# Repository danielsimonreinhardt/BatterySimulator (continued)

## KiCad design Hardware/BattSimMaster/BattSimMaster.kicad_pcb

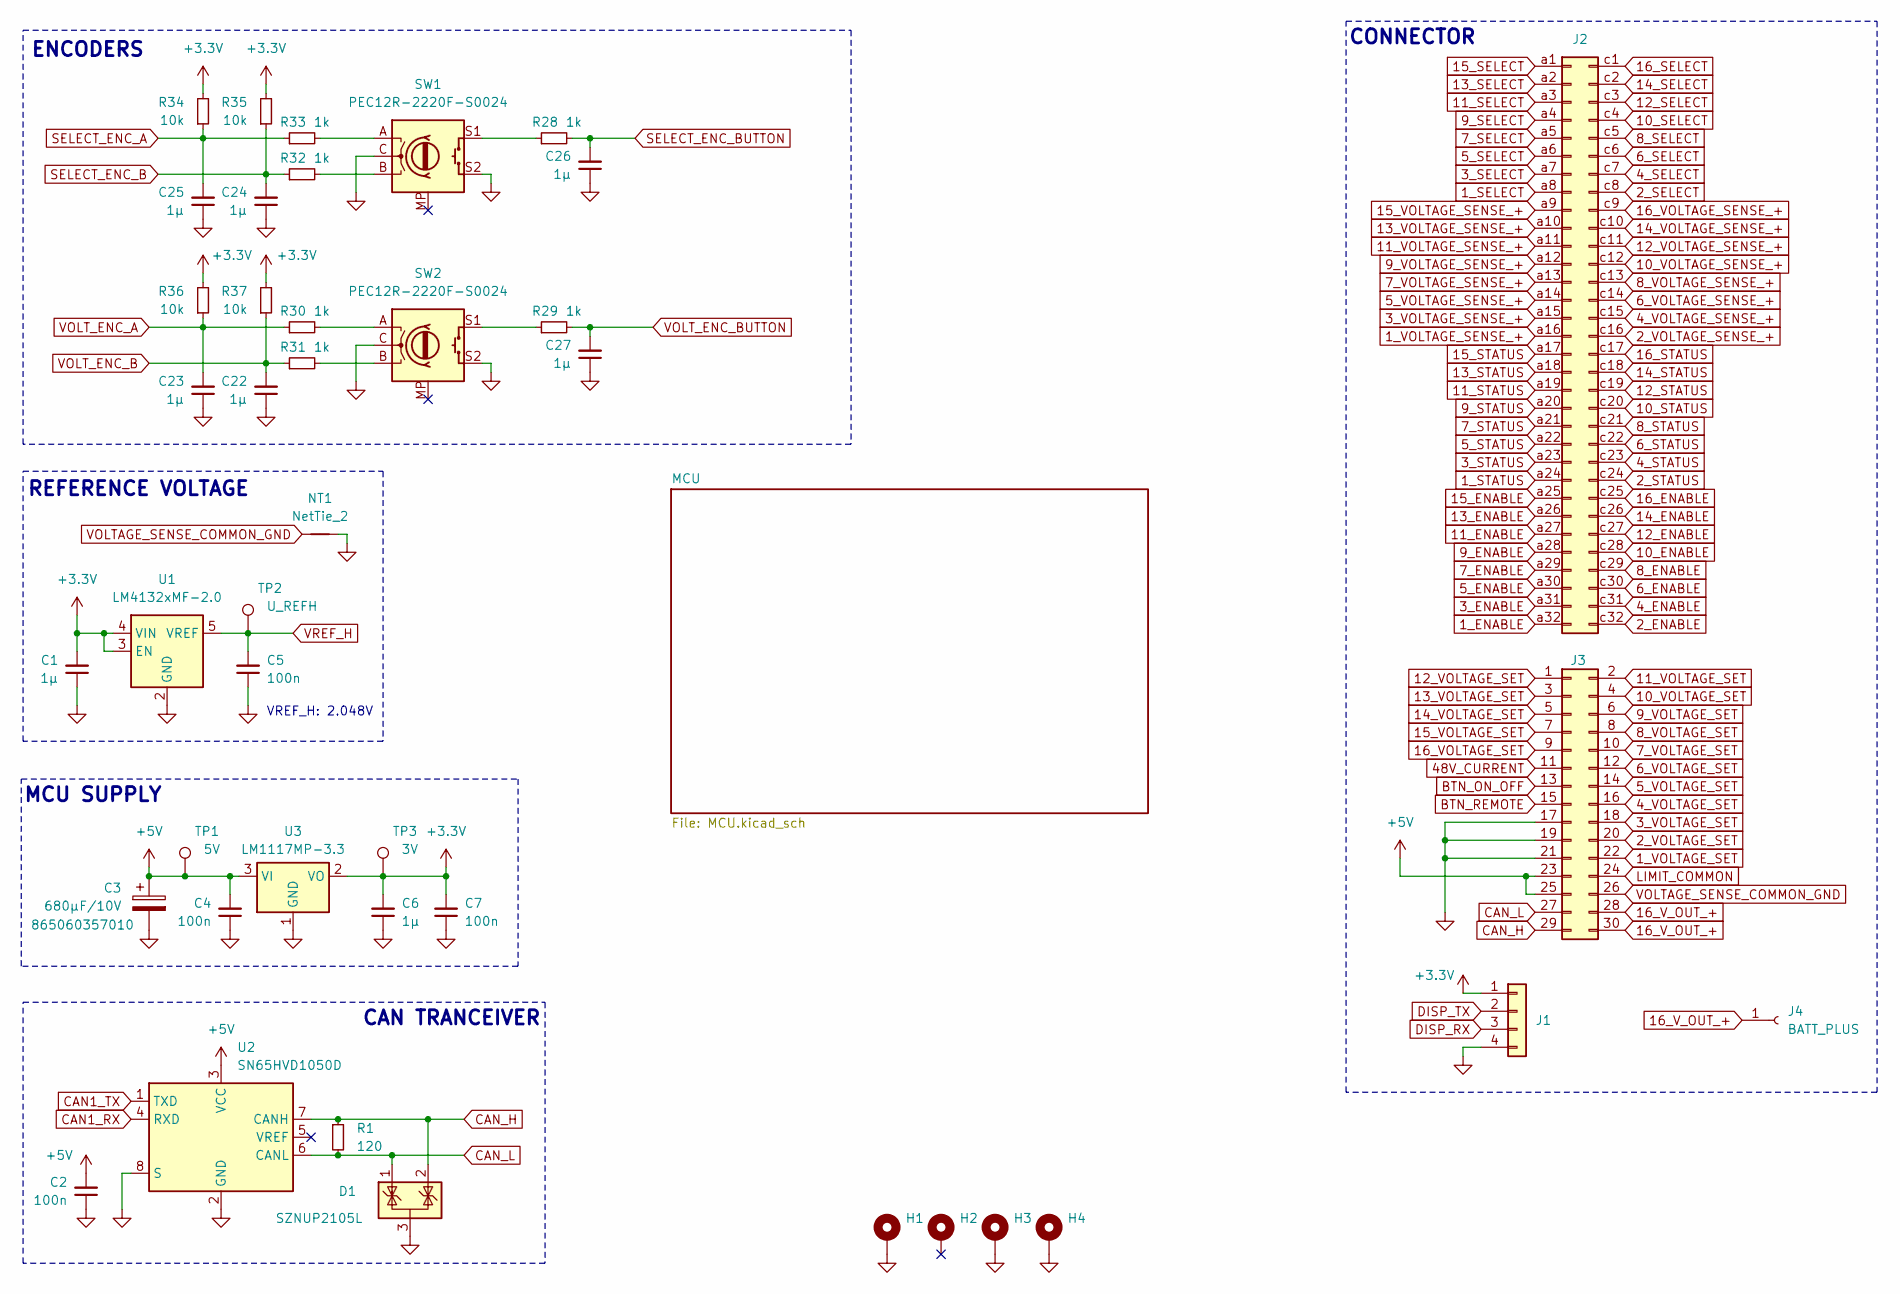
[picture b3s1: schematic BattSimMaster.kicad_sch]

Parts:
C1, C6, C22, C23, C24, C25, C26, C27: 1µ; C_0603_1608Metric_Pad1.08x0.95mm_HandSolder; LCSC Part # C15849
C2, C4, C5, C7: 100n; C_0603_1608Metric_Pad1.08x0.95mm_HandSolder; LCSC Part # C14663
C3: 680µF/10V; CP_Elec_10x10.5
D1: SZNUP2105L; SOT-23
H1, H2, H3, H4: MountingHole_Pad; MountingHole_3.2mm_M3_Pad_Via
J1: Conn_01x04; JST_PH_B4B-PH-K_1x04_P2.00mm_Vertical
J2: DIN41612_02x32_AC; DIN41612_C_2x32_Male_Horizontal_THT
J3: Conn_02x15_Odd_Even; PinSocket_2x15_P2.54mm_Vertical
J4: BATT_PLUS; Banana_Cliff_FCR7350R_S16N-PC_Horizontal
NT1: NetTie_2; NetTie-2_SMD_Pad0.5mm
R1: 120; R_0603_1608Metric_Pad0.98x0.95mm_HandSolder; LCSC C22787
R28, R29, R30, R31, R32, R33: 1k; R_0603_1608Metric; LCSC Part # C21190
R34, R35, R36, R37: 10k; R_0603_1608Metric_Pad0.98x0.95mm_HandSolder; LCSC C25804
SW1, SW2: PEC12R-2220F-S0024; RotaryEncoder_Bourns_Horizontal_PEC12R-2x17F-Sxxxx
TP1: 5V; TestPoint_Pad_D1.0mm
TP2: U_REFH; TestPoint_Pad_D1.0mm
TP3: 3V; TestPoint_Pad_D1.0mm
U1: LM4132xMF-2.0; SOT-23-5; LCSC C2157325
U2: SN65HVD1050D; SOIC-8_3.9x4.9mm_P1.27mm
U3: LM1117MP-3.3; SOT-223-3_TabPin2; LCSC Part # C126027

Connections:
1_ENABLE: J2.a32; also elsewhere on the board
1_SELECT: J2.a8; also elsewhere on the board
1_STATUS: J2.a24; also elsewhere on the board
1_VOLTAGE_SENSE_+: J2.a16; also elsewhere on the board
1_VOLTAGE_SET: J3.22; also elsewhere on the board
2_ENABLE: J2.c32; also elsewhere on the board
2_SELECT: J2.c8; also elsewhere on the board
2_STATUS: J2.c24; also elsewhere on the board
2_VOLTAGE_SENSE_+: J2.c16; also elsewhere on the board
2_VOLTAGE_SET: J3.20; also elsewhere on the board
3_ENABLE: J2.a31; also elsewhere on the board
3_SELECT: J2.a7; also elsewhere on the board
3_STATUS: J2.a23; also elsewhere on the board
3_VOLTAGE_SENSE_+: J2.a15; also elsewhere on the board
3_VOLTAGE_SET: J3.18; also elsewhere on the board
4_ENABLE: J2.c31; also elsewhere on the board
4_SELECT: J2.c7; also elsewhere on the board
4_STATUS: J2.c23; also elsewhere on the board
4_VOLTAGE_SENSE_+: J2.c15; also elsewhere on the board
4_VOLTAGE_SET: J3.16; also elsewhere on the board
5_ENABLE: J2.a30; also elsewhere on the board
5_SELECT: J2.a6; also elsewhere on the board
5_STATUS: J2.a22; also elsewhere on the board
5_VOLTAGE_SENSE_+: J2.a14; also elsewhere on the board
5_VOLTAGE_SET: J3.14; also elsewhere on the board
6_ENABLE: J2.c30; also elsewhere on the board
6_SELECT: J2.c6; also elsewhere on the board
6_STATUS: J2.c22; also elsewhere on the board
6_VOLTAGE_SENSE_+: J2.c14; also elsewhere on the board
6_VOLTAGE_SET: J3.12; also elsewhere on the board
7_ENABLE: J2.a29; also elsewhere on the board
7_SELECT: J2.a5; also elsewhere on the board
7_STATUS: J2.a21; also elsewhere on the board
7_VOLTAGE_SENSE_+: J2.a13; also elsewhere on the board
7_VOLTAGE_SET: J3.10; also elsewhere on the board
8_ENABLE: J2.c29; also elsewhere on the board
8_SELECT: J2.c5; also elsewhere on the board
8_STATUS: J2.c21; also elsewhere on the board
8_VOLTAGE_SENSE_+: J2.c13; also elsewhere on the board
8_VOLTAGE_SET: J3.8; also elsewhere on the board
9_ENABLE: J2.a28; also elsewhere on the board
9_SELECT: J2.a4; also elsewhere on the board
9_STATUS: J2.a20; also elsewhere on the board
9_VOLTAGE_SENSE_+: J2.a12; also elsewhere on the board
9_VOLTAGE_SET: J3.6; also elsewhere on the board
10_ENABLE: J2.c28; also elsewhere on the board
10_SELECT: J2.c4; also elsewhere on the board
10_STATUS: J2.c20; also elsewhere on the board
10_VOLTAGE_SENSE_+: J2.c12; also elsewhere on the board
10_VOLTAGE_SET: J3.4; also elsewhere on the board
11_ENABLE: J2.a27; also elsewhere on the board
11_SELECT: J2.a3; also elsewhere on the board
11_STATUS: J2.a19; also elsewhere on the board
11_VOLTAGE_SENSE_+: J2.a11; also elsewhere on the board
11_VOLTAGE_SET: J3.2; also elsewhere on the board
12_ENABLE: J2.c27; also elsewhere on the board
12_SELECT: J2.c3; also elsewhere on the board
12_STATUS: J2.c19; also elsewhere on the board
12_VOLTAGE_SENSE_+: J2.c11; also elsewhere on the board
12_VOLTAGE_SET: J3.1; also elsewhere on the board
13_ENABLE: J2.a26; also elsewhere on the board
13_SELECT: J2.a2; also elsewhere on the board
13_STATUS: J2.a18; also elsewhere on the board
13_VOLTAGE_SENSE_+: J2.a10; also elsewhere on the board
13_VOLTAGE_SET: J3.3; also elsewhere on the board
14_ENABLE: J2.c26; also elsewhere on the board
14_SELECT: J2.c2; also elsewhere on the board
14_STATUS: J2.c18; also elsewhere on the board
14_VOLTAGE_SENSE_+: J2.c10; also elsewhere on the board
14_VOLTAGE_SET: J3.5; also elsewhere on the board
15_ENABLE: J2.a25; also elsewhere on the board
15_SELECT: J2.a1; also elsewhere on the board
15_STATUS: J2.a17; also elsewhere on the board
15_VOLTAGE_SENSE_+: J2.a9; also elsewhere on the board
15_VOLTAGE_SET: J3.7; also elsewhere on the board
16_ENABLE: J2.c25; also elsewhere on the board
16_SELECT: J2.c1; also elsewhere on the board
16_STATUS: J2.c17; also elsewhere on the board
16_VOLTAGE_SENSE_+: J2.c9; also elsewhere on the board
16_VOLTAGE_SET: J3.9; also elsewhere on the board
16_V_OUT_+: J3.28, J3.30, J4.1
48V_CURRENT: J3.11; also elsewhere on the board
+3.3V: C1.2, C6.2, C7.2, J1.1, R34.2, R35.2, R36.2, R37.2, TP3.1, U1.3 (EN), U1.4 (VIN), U3.2 (VO); also elsewhere on the board
+5V: C2.2, C3.1, C4.2, J3.23, J3.25, TP1.1, U2.3 (VCC), U3.3 (VI)
BTN_ON_OFF: J3.13; also elsewhere on the board
BTN_REMOTE: J3.15; also elsewhere on the board
CAN1_RX: U2.4 (RXD); also elsewhere on the board
CAN1_TX: U2.1 (TXD); also elsewhere on the board
CAN_H: D1.2 (K), J3.29, R1.1, U2.7 (CANH)
CAN_L: D1.1 (K), J3.27, R1.2, U2.6 (CANL)
DISP_RX: J1.3; also elsewhere on the board
DISP_TX: J1.2; also elsewhere on the board
GND: C1.1, C2.1, C3.2, C4.1, C5.1, C6.1, C7.1, C22.1, C23.1, C24.1, C25.1, C26.1, C27.1, D1.3 (A), H1.1, H3.1, H4.1, J1.4, J3.17, J3.19, J3.21, NT1.2, SW1.C, SW1.S2, SW2.C, SW2.S2, U1.2 (GND), U2.2 (GND), U2.8 (S), U3.1 (GND); also elsewhere on the board
LIMIT_COMMON: J3.24; also elsewhere on the board
unnamed: R28.1, SW1.S1
unnamed: R29.1, SW2.S1
unnamed: R30.2, SW2.A
unnamed: R31.2, SW2.B
unnamed: R32.2, SW1.B
unnamed: R33.2, SW1.A
SELECT_ENC_A: C25.2, R33.1, R34.1; also elsewhere on the board
SELECT_ENC_B: C24.2, R32.1, R35.1; also elsewhere on the board
SELECT_ENC_BUTTON: C26.2, R28.2; also elsewhere on the board
VOLTAGE_SENSE_COMMON_GND: J3.26, NT1.1
VOLT_ENC_A: C23.2, R30.1, R36.1; also elsewhere on the board
VOLT_ENC_B: C22.2, R31.1, R37.1; also elsewhere on the board
VOLT_ENC_BUTTON: C27.2, R29.2; also elsewhere on the board
VREF_H: C5.2, TP2.1, U1.5 (VREF); also elsewhere on the board

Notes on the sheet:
MCU SUPPLY
CONNECTOR
CAN TRANCEIVER
VREF_H: 2.048V
REFERENCE VOLTAGE
ENCODERS

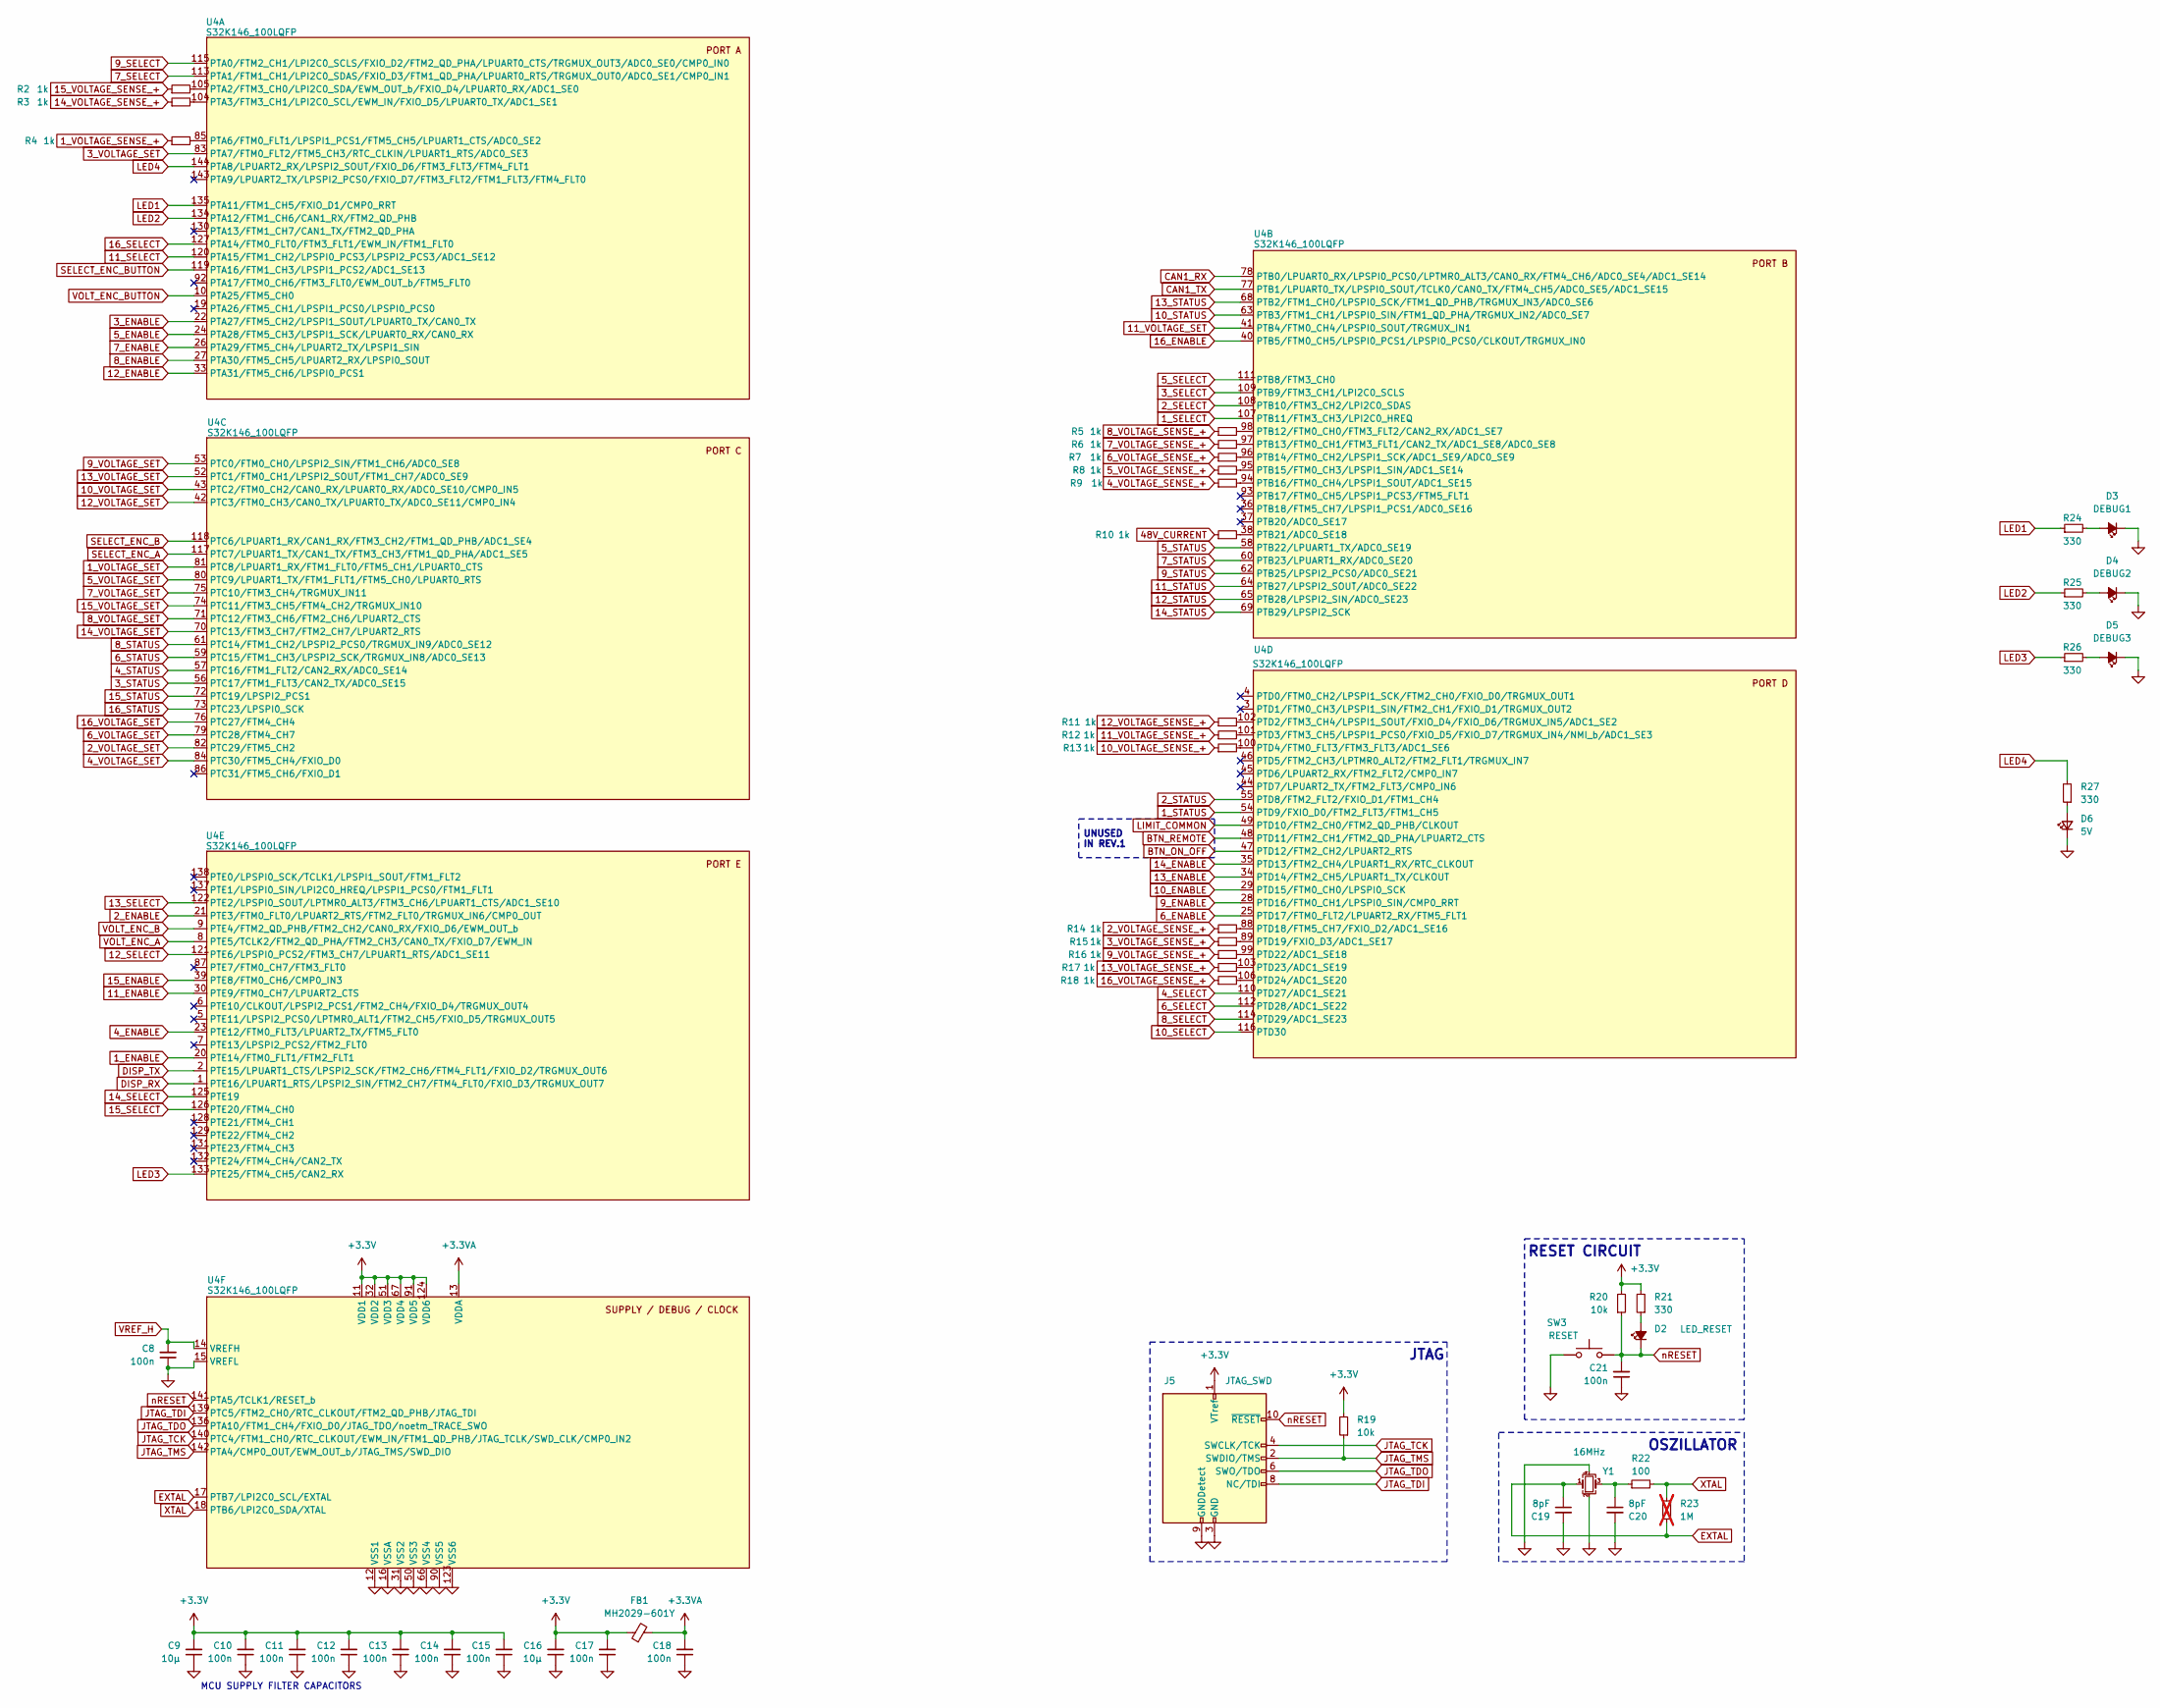
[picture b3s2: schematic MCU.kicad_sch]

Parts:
C8, C10, C11, C12, C13, C14, C15, C17, C18: 100n; C_0603_1608Metric_Pad1.08x0.95mm_HandSolder; LCSC Part # C14663
C9, C16: 10µ; C_0805_2012Metric_Pad1.18x1.45mm_HandSolder; LCSC Part # C15850
C19, C20: 8pF; C_0603_1608Metric_Pad1.08x0.95mm_HandSolder
C21: 100n; C_0603_1608Metric_Pad1.08x0.95mm_HandSolder; LCSC C14663
D2: LED_RESET; LED_0805_2012Metric_Pad1.15x1.40mm_HandSolder; LCSC C2296
D3: DEBUG1; LED_0805_2012Metric; LCSC C2296
D4: DEBUG2; LED_0805_2012Metric
D5: DEBUG3; LED_0805_2012Metric
D6: 5V; LED_D3.0mm_Horizontal_O1.27mm_Z6.0mm
FB1: MH2029-601Y; L_0805_2012Metric_Pad1.05x1.20mm_HandSolder; LCSC Part # C840592
J5: JTAG_SWD; SAMTEC_FTSH-105-01-F-DV-P-TR; LCSC Part # C5136979
R2, R3, R4, R5, R6, R7, R8, R9, R10, R11, R12, R13, R14, R15, R16, R17, R18: 1k; R_0603_1608Metric; LCSC Part # C21190
R19, R20: 10k; R_0603_1608Metric_Pad0.98x0.95mm_HandSolder; LCSC C25804
R21: 330; R_0603_1608Metric_Pad0.98x0.95mm_HandSolder; LCSC C23138
R22: 100; R_0603_1608Metric_Pad0.98x0.95mm_HandSolder
R23: 1M; R_0402_1005Metric_Pad0.72x0.64mm_HandSolder; not fitted
R24, R25, R26: 330; R_0603_1608Metric; LCSC C23138
R27: 330; R_0603_1608Metric
SW3: RESET; SW_PUSH_6mm
U4: S32K146_100LQFP; LQFP-144_20x20mm_P0.5mm; LCSC Part # C427701
Y1: 16MHz; Crystal_SMD_3225-4Pin_3.2x2.5mm; LCSC C13738

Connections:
1_ENABLE: U4.20 (PTE14/FTM0_FLT1/FTM2_FLT1); also elsewhere on the board
1_SELECT: U4.107 (PTB11/FTM3_CH3/LPI2C0_HREQ); also elsewhere on the board
1_STATUS: U4.54 (PTD9/FXIO_D0/FTM2_FLT3/FTM1_CH5); also elsewhere on the board
1_VOLTAGE_SENSE_+: R4.1; also elsewhere on the board
1_VOLTAGE_SET: U4.81 (PTC8/LPUART1_RX/FTM1_FLT0/FTM5_CH1/LPUA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); also elsewhere on the board
2_ENABLE: U4.21 (PTE3/FTM0_FLT0/LPUART2_RTS/FTM2_FLT0/TR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); also elsewhere on the board
2_SELECT: U4.108 (PTB10/FTM3_CH2/LPI2C0_SDAS); also elsewhere on the board
2_STATUS: U4.55 (PTD8/FTM2_FLT2/FXIO_D1/FTM1_CH4); also elsewhere on the board
2_VOLTAGE_SENSE_+: R14.1; also elsewhere on the board
2_VOLTAGE_SET: U4.82 (PTC29/FTM5_CH2); also elsewhere on the board
3_ENABLE: U4.22 (PTA27/FTM5_CH2/LPSPI1_SOUT/LPUART0_TX/C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); also elsewhere on the board
3_SELECT: U4.109 (PTB9/FTM3_CH1/LPI2C0_SCLS); also elsewhere on the board
3_STATUS: U4.56 (PTC17/FTM1_FLT3/CAN2_TX/ADC0_SE15); also elsewhere on the board
3_VOLTAGE_SENSE_+: R15.1; also elsewhere on the board
3_VOLTAGE_SET: U4.83 (PTA7/FTM0_FLT2/FTM5_CH3/RTC_CLKIN/LPUAR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); also elsewhere on the board
4_ENABLE: U4.23 (PTE12/FTM0_FLT3/LPUART2_TX/FTM5_FLT0); also elsewhere on the board
4_SELECT: U4.110 (PTD27/ADC1_SE21); also elsewhere on the board
4_STATUS: U4.57 (PTC16/FTM1_FLT2/CAN2_RX/ADC0_SE14); also elsewhere on the board
4_VOLTAGE_SENSE_+: R9.1; also elsewhere on the board
4_VOLTAGE_SET: U4.84 (PTC30/FTM5_CH4/FXIO_D0); also elsewhere on the board
5_ENABLE: U4.24 (PTA28/FTM5_CH3/LPSPI1_SCK/LPUART0_RX/CA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); also elsewhere on the board
5_SELECT: U4.111 (PTB8/FTM3_CH0); also elsewhere on the board
5_STATUS: U4.58 (PTB22/LPUART1_TX/ADC0_SE19); also elsewhere on the board
5_VOLTAGE_SENSE_+: R8.1; also elsewhere on the board
5_VOLTAGE_SET: U4.80 (PTC9/LPUART1_TX/FTM1_FLT1/FTM5_CH0/LPUA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); also elsewhere on the board
6_ENABLE: U4.25 (PTD17/FTM0_FLT2/LPUART2_RX/FTM5_FLT1); also elsewhere on the board
6_SELECT: U4.112 (PTD28/ADC1_SE22); also elsewhere on the board
6_STATUS: U4.59 (PTC15/FTM1_CH3/LPSPI2_SCK/TRGMUX_IN8/AD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); also elsewhere on the board
6_VOLTAGE_SENSE_+: R7.1; also elsewhere on the board
6_VOLTAGE_SET: U4.79 (PTC28/FTM4_CH7); also elsewhere on the board
7_ENABLE: U4.26 (PTA29/FTM5_CH4/LPUART2_TX/LPSPI1_SIN); also elsewhere on the board
7_SELECT: U4.113 (PTA1/FTM1_CH1/LPI2C0_SDAS/FXIO_D3/FTM1_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); also elsewhere on the board
7_STATUS: U4.60 (PTB23/LPUART1_RX/ADC0_SE20); also elsewhere on the board
7_VOLTAGE_SENSE_+: R6.1; also elsewhere on the board
7_VOLTAGE_SET: U4.75 (PTC10/FTM3_CH4/TRGMUX_IN11); also elsewhere on the board
8_ENABLE: U4.27 (PTA30/FTM5_CH5/LPUART2_RX/LPSPI0_SOUT); also elsewhere on the board
8_SELECT: U4.114 (PTD29/ADC1_SE23); also elsewhere on the board
8_STATUS: U4.61 (PTC14/FTM1_CH2/LPSPI2_PCS0/TRGMUX_IN9/A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); also elsewhere on the board
8_VOLTAGE_SENSE_+: R5.1; also elsewhere on the board
8_VOLTAGE_SET: U4.71 (PTC12/FTM3_CH6/FTM2_CH6/LPUART2_CTS); also elsewhere on the board
9_ENABLE: U4.28 (PTD16/FTM0_CH1/LPSPI0_SIN/CMP0_RRT); also elsewhere on the board
9_SELECT: U4.115 (PTA0/FTM2_CH1/LPI2C0_SCLS/FXIO_D2/FTM2_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); also elsewhere on the board
9_STATUS: U4.62 (PTB25/LPSPI2_PCS0/ADC0_SE21); also elsewhere on the board
9_VOLTAGE_SENSE_+: R16.1; also elsewhere on the board
9_VOLTAGE_SET: U4.53 (PTC0/FTM0_CH0/LPSPI2_SIN/FTM1_CH6/ADC0_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); also elsewhere on the board
10_ENABLE: U4.29 (PTD15/FTM0_CH0/LPSPI0_SCK); also elsewhere on the board
10_SELECT: U4.116 (PTD30); also elsewhere on the board
10_STATUS: U4.63 (PTB3/FTM1_CH1/LPSPI0_SIN/FTM1_QD_PHA/TR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); also elsewhere on the board
10_VOLTAGE_SENSE_+: R13.1; also elsewhere on the board
10_VOLTAGE_SET: U4.43 (PTC2/FTM0_CH2/CAN0_RX/LPUART0_RX/ADC0_S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); also elsewhere on the board
11_ENABLE: U4.30 (PTE9/FTM0_CH7/LPUART2_CTS); also elsewhere on the board
11_SELECT: U4.120 (PTA15/FTM1_CH2/LPSPI0_PCS3/LPSPI2_PCS3/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); also elsewhere on the board
11_STATUS: U4.64 (PTB27/LPSPI2_SOUT/ADC0_SE22); also elsewhere on the board
11_VOLTAGE_SENSE_+: R12.1; also elsewhere on the board
11_VOLTAGE_SET: U4.41 (PTB4/FTM0_CH4/LPSPI0_SOUT/TRGMUX_IN1); also elsewhere on the board
12_ENABLE: U4.33 (PTA31/FTM5_CH6/LPSPI0_PCS1); also elsewhere on the board
12_SELECT: U4.121 (PTE6/LPSPI0_PCS2/FTM3_CH7/LPUART1_RTS/A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); also elsewhere on the board
12_STATUS: U4.65 (PTB28/LPSPI2_SIN/ADC0_SE23); also elsewhere on the board
12_VOLTAGE_SENSE_+: R11.1; also elsewhere on the board
12_VOLTAGE_SET: U4.42 (PTC3/FTM0_CH3/CAN0_TX/LPUART0_TX/ADC0_S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); also elsewhere on the board
13_ENABLE: U4.34 (PTD14/FTM2_CH5/LPUART1_TX/CLKOUT); also elsewhere on the board
13_SELECT: U4.122 (PTE2/LPSPI0_SOUT/LPTMR0_ALT3/FTM3_CH6/L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); also elsewhere on the board
13_STATUS: U4.68 (PTB2/FTM1_CH0/LPSPI0_SCK/FTM1_QD_PHB/TR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); also elsewhere on the board
13_VOLTAGE_SENSE_+: R17.1; also elsewhere on the board
13_VOLTAGE_SET: U4.52 (PTC1/FTM0_CH1/LPSPI2_SOUT/FTM1_CH7/ADC0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); also elsewhere on the board
14_ENABLE: U4.35 (PTD13/FTM2_CH4/LPUART1_RX/RTC_CLKOUT); also elsewhere on the board
14_SELECT: U4.125 (PTE19); also elsewhere on the board
14_STATUS: U4.69 (PTB29/LPSPI2_SCK); also elsewhere on the board
14_VOLTAGE_SENSE_+: R3.1; also elsewhere on the board
14_VOLTAGE_SET: U4.70 (PTC13/FTM3_CH7/FTM2_CH7/LPUART2_RTS); also elsewhere on the board
15_ENABLE: U4.39 (PTE8/FTM0_CH6/CMP0_IN3); also elsewhere on the board
15_SELECT: U4.126 (PTE20/FTM4_CH0); also elsewhere on the board
15_STATUS: U4.72 (PTC19/LPSPI2_PCS1); also elsewhere on the board
15_VOLTAGE_SENSE_+: R2.1; also elsewhere on the board
15_VOLTAGE_SET: U4.74 (PTC11/FTM3_CH5/FTM4_CH2/TRGMUX_IN10); also elsewhere on the board
16_ENABLE: U4.40 (PTB5/FTM0_CH5/LPSPI0_PCS1/LPSPI0_PCS0/C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); also elsewhere on the board
16_SELECT: U4.127 (PTA14/FTM0_FLT0/FTM3_FLT1/EWM_IN/FTM1_F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); also elsewhere on the board
16_STATUS: U4.73 (PTC23/LPSPI0_SCK); also elsewhere on the board
16_VOLTAGE_SENSE_+: R18.1; also elsewhere on the board
16_VOLTAGE_SET: U4.76 (PTC27/FTM4_CH4); also elsewhere on the board
48V_CURRENT: R10.1; also elsewhere on the board
+3.3V: C9.2, C10.2, C11.2, C12.2, C13.2, C14.2, C15.2, C16.2, C17.2, FB1.1, J5.1 (VTref), R19.2, R20.2, R21.2, U4.11 (VDD1), U4.32 (VDD2), U4.51 (VDD3), U4.67 (VDD4), U4.91 (VDD5), U4.124 (VDD6); also elsewhere on the board
+3.3VA: C18.2, FB1.2, U4.13 (VDDA)
BTN_ON_OFF: U4.47 (PTD12/FTM2_CH2/LPUART2_RTS); also elsewhere on the board
BTN_REMOTE: U4.48 (PTD11/FTM2_CH1/FTM2_QD_PHA/LPUART2_CTS); also elsewhere on the board
CAN1_RX: U4.78 (PTB0/LPUART0_RX/LPSPI0_PCS0/LPTMR0_ALT3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); also elsewhere on the board
CAN1_TX: U4.77 (PTB1/LPUART0_TX/LPSPI0_SOUT/TCLK0/CAN0_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); also elsewhere on the board
DISP_RX: U4.1 (PTE16/LPUART1_RTS/LPSPI2_SIN/FTM2_CH7/F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); also elsewhere on the board
DISP_TX: U4.2 (PTE15/LPUART1_CTS/LPSPI2_SCK/FTM2_CH6/F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); also elsewhere on the board
EXTAL: C19.1, R23.1, U4.17 (PTB7/LPI2C0_SCL/EXTAL), Y1.1
GND: C8.1, C9.1, C10.1, C11.1, C12.1, C13.1, C14.1, C15.1, C16.1, C17.1, C18.1, C19.2, C20.2, C21.1, D3.1 (K), D4.1 (K), D5.1 (K), D6.1 (K), J5.3 (GND), J5.5 (GND), J5.9 (GNDDetect), SW3.1, U4.12 (VSS1), U4.15 (VREFL), U4.16 (VSSA), U4.31 (VSS2), U4.50 (VSS3), U4.66 (VSS4), U4.90 (VSS5), U4.123 (VSS6), Y1.2, Y1.4; also elsewhere on the board
JTAG_TCK: J5.4 (SWCLK/TCK), U4.140 (PTC4/FTM1_CH0/RTC_CLKOUT/EWM_IN/FTM1_QD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)
JTAG_TDI: J5.8 (NC/TDI), U4.139 (PTC5/FTM2_CH0/RTC_CLKOUT/FTM2_QD_PHB/JT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)
JTAG_TDO: J5.6 (SWO/TDO), U4.136 (PTA10/FTM1_CH4/FXIO_D0/JTAG_TDO/noetm_T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)
JTAG_TMS: J5.2 (SWDIO/TMS), R19.1, U4.142 (PTA4/CMP0_OUT/EWM_OUT_b/JTAG_TMS/SWD_DIO)
LED1: R24.1, U4.135 (PTA11/FTM1_CH5/FXIO_D1/CMP0_RRT)
LED2: R25.1, U4.134 (PTA12/FTM1_CH6/CAN1_RX/FTM2_QD_PHB)
LED3: R26.1, U4.133 (PTE25/FTM4_CH5/CAN2_RX)
LED4: R27.2, U4.144 (PTA8/LPUART2_RX/LPSPI2_SOUT/FXIO_D6/FTM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)
LIMIT_COMMON: U4.49 (PTD10/FTM2_CH0/FTM2_QD_PHB/CLKOUT); also elsewhere on the board
unnamed: C20.1, R22.1, Y1.3
unnamed: D2.2 (A), R21.1
unnamed: D3.2 (A), R24.2
unnamed: D4.2 (A), R25.2
unnamed: D5.2 (A), R26.2
unnamed: D6.2 (A), R27.1
unnamed: R2.2, U4.105 (PTA2/FTM3_CH0/LPI2C0_SDA/EWM_OUT_b/FXIO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)
unnamed: R3.2, U4.104 (PTA3/FTM3_CH1/LPI2C0_SCL/EWM_IN/FXIO_D5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)
unnamed: R4.2, U4.85 (PTA6/FTM0_FLT1/LPSPI1_PCS1/FTM5_CH5/LPU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)
unnamed: R5.2, U4.98 (PTB12/FTM0_CH0/FTM3_FLT2/CAN2_RX/ADC1_S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)
unnamed: R6.2, U4.97 (PTB13/FTM0_CH1/FTM3_FLT1/CAN2_TX/ADC1_S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)
unnamed: R7.2, U4.96 (PTB14/FTM0_CH2/LPSPI1_SCK/ADC1_SE9/ADC0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)
unnamed: R8.2, U4.95 (PTB15/FTM0_CH3/LPSPI1_SIN/ADC1_SE14)
unnamed: R9.2, U4.94 (PTB16/FTM0_CH4/LPSPI1_SOUT/ADC1_SE15)
unnamed: R10.2, U4.38 (PTB21/ADC0_SE18)
unnamed: R11.2, U4.102 (PTD2/FTM3_CH4/LPSPI1_SOUT/FXIO_D4/FXIO_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)
unnamed: R12.2, U4.101 (PTD3/FTM3_CH5/LPSPI1_PCS0/FXIO_D5/FXIO_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)
unnamed: R13.2, U4.100 (PTD4/FTM0_FLT3/FTM3_FLT3/ADC1_SE6)
unnamed: R14.2, U4.88 (PTD18/FTM5_CH7/FXIO_D2/ADC1_SE16)
unnamed: R15.2, U4.89 (PTD19/FXIO_D3/ADC1_SE17)
unnamed: R16.2, U4.99 (PTD22/ADC1_SE18)
unnamed: R17.2, U4.103 (PTD23/ADC1_SE19)
unnamed: R18.2, U4.106 (PTD24/ADC1_SE20)
SELECT_ENC_A: U4.117 (PTC7/LPUART1_TX/CAN1_TX/FTM3_CH3/FTM1_Q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); also elsewhere on the board
SELECT_ENC_B: U4.118 (PTC6/LPUART1_RX/CAN1_RX/FTM3_CH2/FTM1_Q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); also elsewhere on the board
SELECT_ENC_BUTTON: U4.119 (PTA16/FTM1_CH3/LPSPI1_PCS2/ADC1_SE13); also elsewhere on the board
VOLT_ENC_A: U4.8 (PTE5/TCLK2/FTM2_QD_PHA/FTM2_CH3/CAN0_TX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); also elsewhere on the board
VOLT_ENC_B: U4.9 (PTE4/FTM2_QD_PHB/FTM2_CH2/CAN0_RX/FXIO_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); also elsewhere on the board
VOLT_ENC_BUTTON: U4.10 (PTA25/FTM5_CH0); also elsewhere on the board
VREF_H: C8.2, U4.14 (VREFH); also elsewhere on the board
XTAL: R22.2, R23.2, U4.18 (PTB6/LPI2C0_SDA/XTAL)
nRESET: C21.2, D2.1 (K), J5.10 (~RESET), R20.1, SW3.2, U4.141 (PTA5/TCLK1/RESET_b)

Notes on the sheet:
OSZILLATOR
UNUSED IN REV.1
JTAG
MCU SUPPLY FILTER CAPACITORS
RESET CIRCUIT

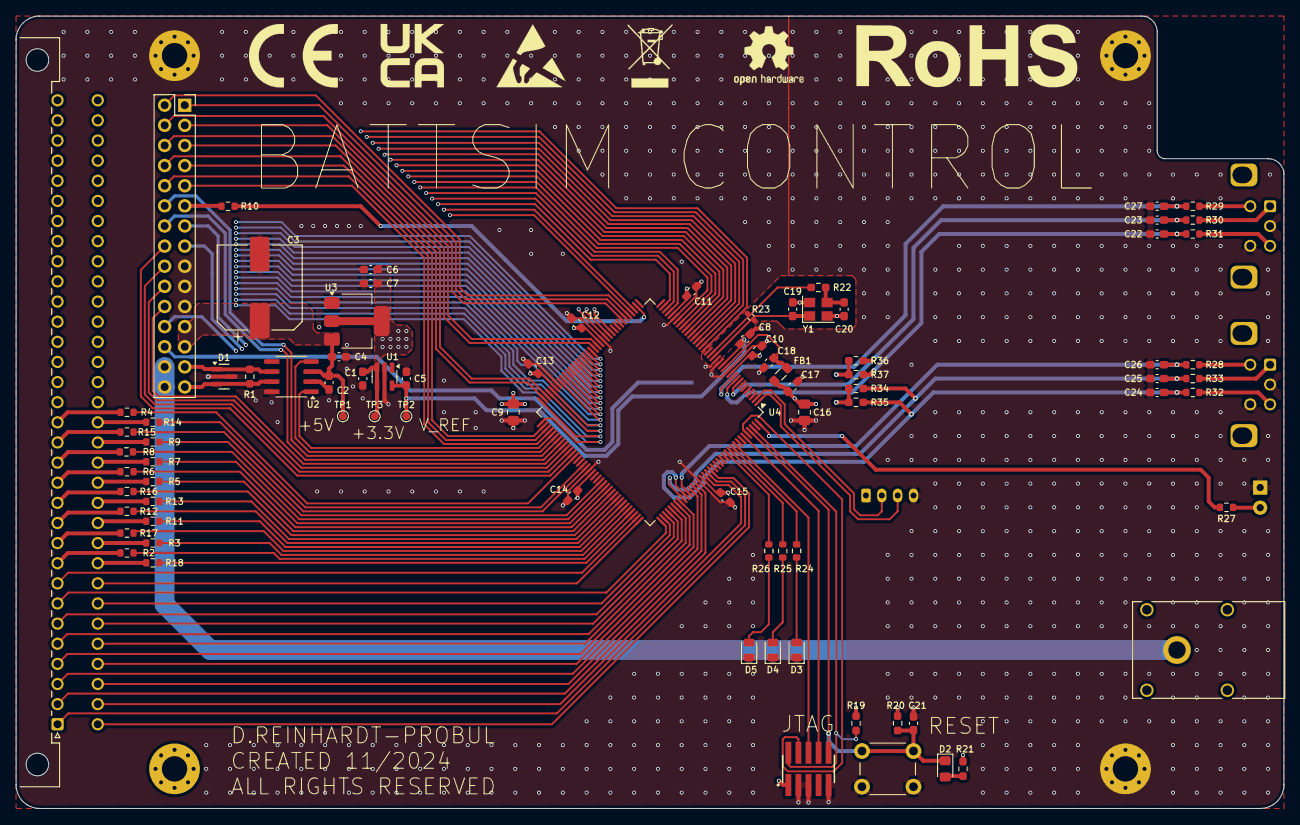
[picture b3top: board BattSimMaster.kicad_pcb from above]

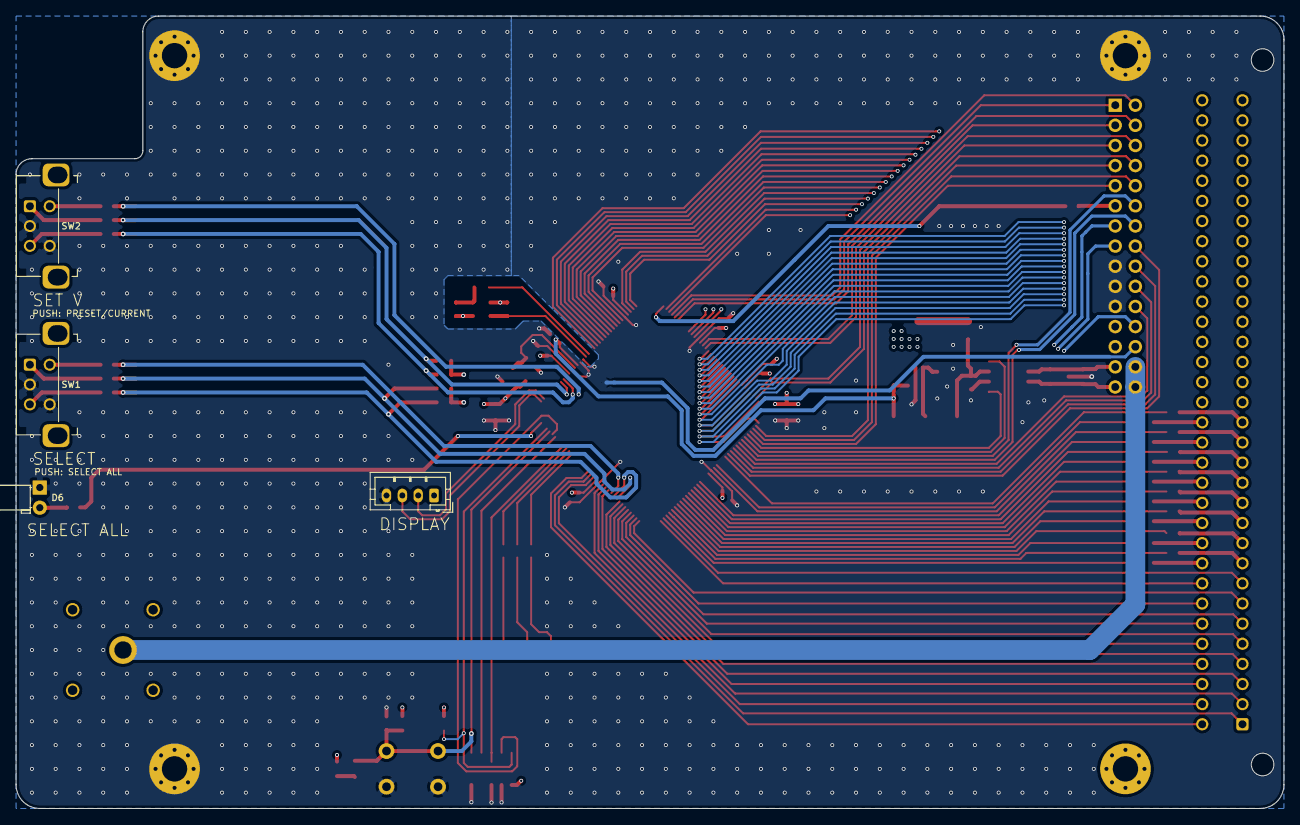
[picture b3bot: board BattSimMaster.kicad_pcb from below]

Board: 4 copper layers, 160.0 x 100.0 mm, 92 parts (5 on the bottom side), 143 nets.
